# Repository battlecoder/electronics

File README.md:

# electronics
Small Hardware projects that you will most likely find described in my blog: blog.damnsoft.org

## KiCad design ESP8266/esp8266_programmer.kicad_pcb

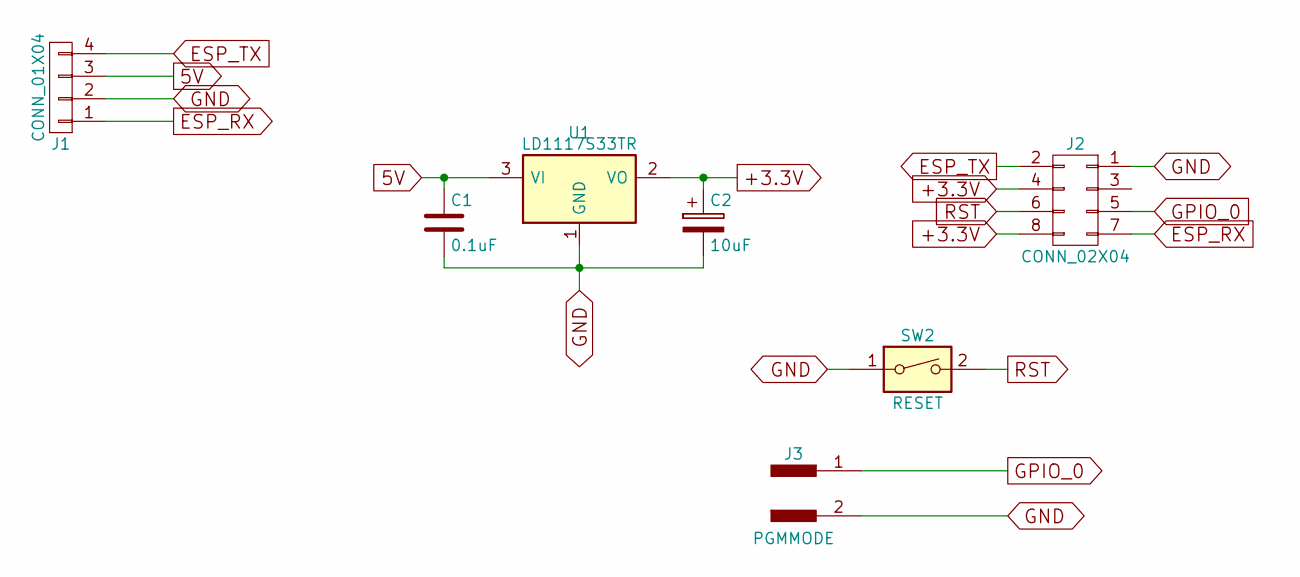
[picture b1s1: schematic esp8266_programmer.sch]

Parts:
C1: 0.1uF; C_Disc_D5.0mm_W2.5mm_P2.50mm
C2: 10uF; CP_Radial_D5.0mm_P2.50mm
J1: CONN_01X04; Pin_Header_Angled_1x04_Pitch2.54mm
J2: CONN_02X04; Socket_Strip_Straight_2x04_Pitch2.54mm
J3: PGMMODE; Pin_Header_Straight_1x02_Pitch2.54mm
SW2: RESET; SW_PUSH_6mm
U1: LD1117S33TR; TO-220-3_Vertical

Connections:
5V: C1.1, J1.3, U1.3 (VI)
+3.3V: C2.1, J2.4, J2.8, U1.2 (VO)
ESP_RX: J1.1, J2.7
ESP_TX: J1.4, J2.2
GND: C1.2, C2.2, J1.2, J2.1, J3.2, SW2.1, U1.1 (GND)
GPIO_0: J2.5, J3.1
RST: J2.6, SW2.2

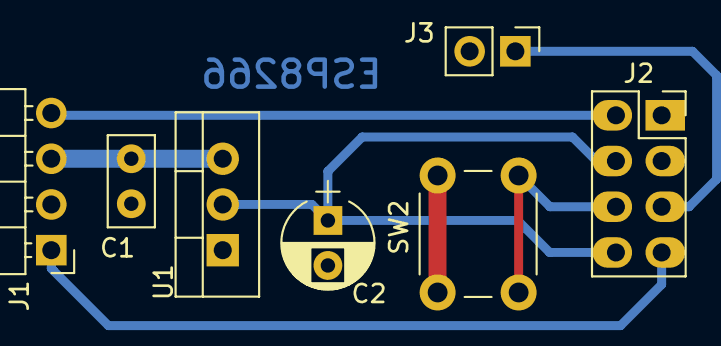
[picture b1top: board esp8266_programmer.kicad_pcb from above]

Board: 2 copper layers, 7 parts (0 on the bottom side), 7 nets.

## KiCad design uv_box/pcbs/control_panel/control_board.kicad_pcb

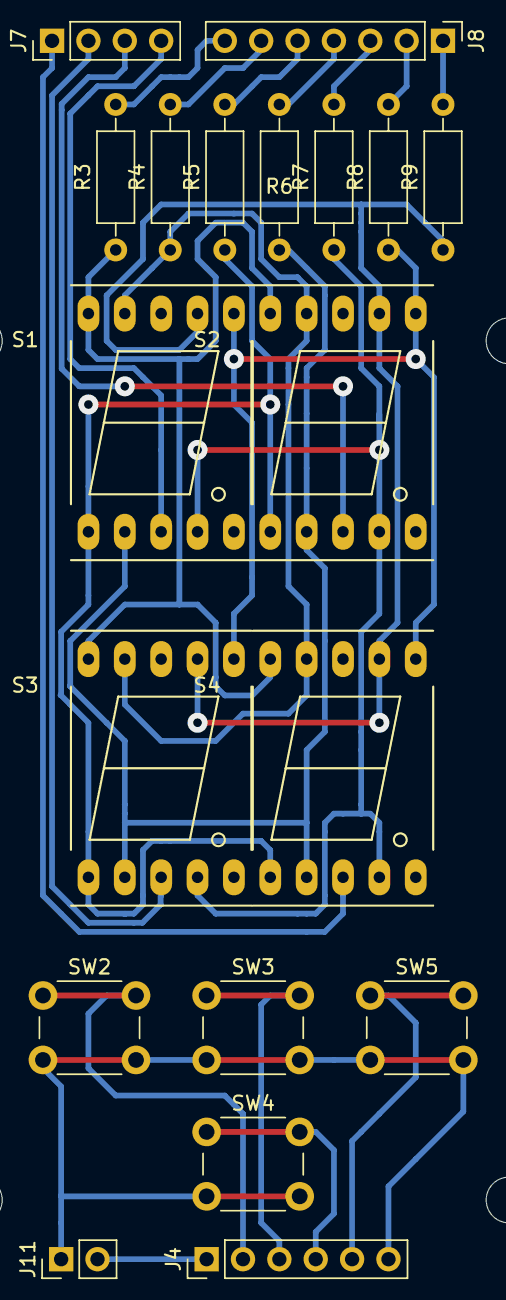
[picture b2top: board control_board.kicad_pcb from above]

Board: 2 copper layers, 19 parts (0 on the bottom side), 24 nets.

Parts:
J4: INPUTS2; Pin_Header_Straight_1x06_Pitch2.54mm
J7: 7SEG_DIGITS2; Pin_Header_Straight_1x04_Pitch2.54mm
J8: 7SEG_SEGMENTS2; Pin_Header_Straight_1x07_Pitch2.54mm
J11: REED; Pin_Header_Straight_1x02_Pitch2.54mm
R3, R4, R5, R6, R7, R8, R9: 100; R_Axial_DIN0207_L6.3mm_D2.5mm_P10.16mm_Horizontal
S1, S2, S3, S4: 7SEGM; 7SegmentLED_LTS6760_LTS6780
SW2, SW3, SW4, SW5: SW_Push; SW_PUSH_6mm

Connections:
DIG1: J7.4, S1.3
DIG2: J7.3, S2.3
DIG3: J7.2, S3.3
DIG4: J7.1, S4.3
unnamed: J4.2, SW2.1
unnamed: J4.3, SW3.1
unnamed: J4.4, SW4.1
unnamed: J4.5, SW5.1
unnamed: J8.1, R9.2
unnamed: J8.2, R8.2
unnamed: J8.3, R7.2
unnamed: J8.4, R6.2
unnamed: J8.5, R5.2
unnamed: J8.6, R4.2
unnamed: J8.7, R3.2
unnamed: J4.6, J11.1, SW2.2, SW3.2, SW4.2, SW5.2
unnamed: J4.1, J11.2
SEG1: R9.1, S1.7, S2.7, S3.7, S4.7
SEG2: R8.1, S1.6, S2.6, S3.6, S4.6
SEG3: R7.1, S1.4, S2.4, S3.4, S4.4
SEG4: R6.1, S1.2, S2.2, S3.2, S4.2
SEG5: R5.1, S1.1, S2.1, S3.1, S4.1
SEG6: R4.1, S1.9, S2.9, S3.9, S4.9
SEG7: R3.1, S1.10, S2.10, S3.10, S4.10

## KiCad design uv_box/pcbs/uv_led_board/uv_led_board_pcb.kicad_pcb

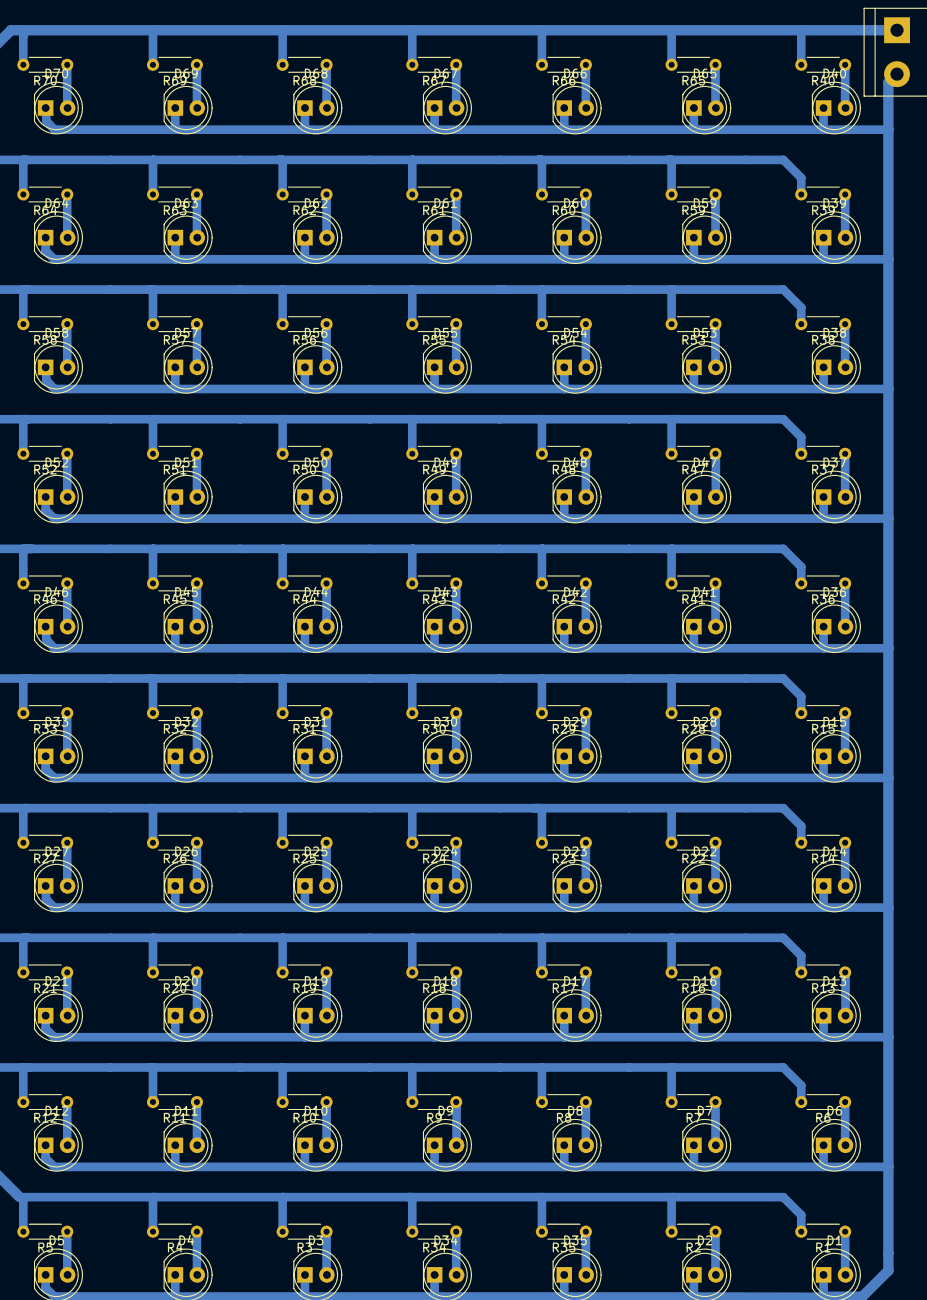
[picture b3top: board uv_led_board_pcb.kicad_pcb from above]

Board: 2 copper layers, 141 parts (0 on the bottom side), 72 nets.

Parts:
D1, D2, D3, D4, D5, D6, D7, D8, D9, D10, D11, D12, D13, D14, D15, D16, D17, D18, D19, D20, D21, D22, D23, D24, D25, D26, D27, D28, D29, D30, D31, D32, D33, D34, D35, D36, D37, D38, D39, D40, D41, D42, D43, D44, D45, D46, D47, D48, D49, D50, D51, D52, D53, D54, D55, D56, D57, D58, D59, D60, D61, D62, D63, D64, D65, D66, D67, D68, D69, D70: LED; LED_D5.0mm
J1: Screw_Terminal_1x02; bornier2
R1, R2, R3, R4, R5, R6, R7, R8, R9, R10, R11, R12, R13, R14, R15, R16, R17, R18, R19, R20, R21, R22, R23, R24, R25, R26, R27, R28, R29, R30, R31, R32, R33, R34, R35, R36, R37, R38, R39, R40, R41, R42, R43, R44, R45, R46, R47, R48, R49, R50, R51, R52, R53, R54, R55, R56, R57, R58, R59, R60, R61, R62, R63, R64, R65, R66, R67, R68, R69, R70: 100; R_Axial_DIN0204_L3.6mm_D1.6mm_P5.08mm_Horizontal

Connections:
+5V: J1.1, R1.2, R2.2, R3.2, R4.2, R5.2, R6.2, R7.2, R8.2, R9.2, R10.2, R11.2, R12.2, R13.2, R14.2, R15.2, R16.2, R17.2, R18.2, R19.2, R20.2, R21.2, R22.2, R23.2, R24.2, R25.2, R26.2, R27.2, R28.2, R29.2, R30.2, R31.2, R32.2, R33.2, R34.2, R35.2, R36.2, R37.2, R38.2, R39.2, R40.2, R41.2, R42.2, R43.2, R44.2, R45.2, R46.2, R47.2, R48.2, R49.2, R50.2, R51.2, R52.2, R53.2, R54.2, R55.2, R56.2, R57.2, R58.2, R59.2, R60.2, R61.2, R62.2, R63.2, R64.2, R65.2, R66.2, R67.2, R68.2, R69.2, R70.2
GND: D1.1, D2.1, D3.1, D4.1, D5.1, D6.1, D7.1, D8.1, D9.1, D10.1, D11.1, D12.1, D13.1, D14.1, D15.1, D16.1, D17.1, D18.1, D19.1, D20.1, D21.1, D22.1, D23.1, D24.1, D25.1, D26.1, D27.1, D28.1, D29.1, D30.1, D31.1, D32.1, D33.1, D34.1, D35.1, D36.1, D37.1, D38.1, D39.1, D40.1, D41.1, D42.1, D43.1, D44.1, D45.1, D46.1, D47.1, D48.1, D49.1, D50.1, D51.1, D52.1, D53.1, D54.1, D55.1, D56.1, D57.1, D58.1, D59.1, D60.1, D61.1, D62.1, D63.1, D64.1, D65.1, D66.1, D67.1, D68.1, D69.1, D70.1, J1.2
unnamed: D1.2, R1.1
unnamed: D2.2, R2.1
unnamed: D3.2, R3.1
unnamed: D4.2, R4.1
unnamed: D5.2, R5.1
unnamed: D6.2, R6.1
unnamed: D7.2, R7.1
unnamed: D8.2, R8.1
unnamed: D9.2, R9.1
unnamed: D10.2, R10.1
unnamed: D11.2, R11.1
unnamed: D12.2, R12.1
unnamed: D13.2, R13.1
unnamed: D14.2, R14.1
unnamed: D15.2, R15.1
unnamed: D16.2, R16.1
unnamed: D17.2, R17.1
unnamed: D18.2, R18.1
unnamed: D19.2, R19.1
unnamed: D20.2, R20.1
unnamed: D21.2, R21.1
unnamed: D22.2, R22.1
unnamed: D23.2, R23.1
unnamed: D24.2, R24.1
unnamed: D25.2, R25.1
unnamed: D26.2, R26.1
unnamed: D27.2, R27.1
unnamed: D28.2, R28.1
unnamed: D29.2, R29.1
unnamed: D30.2, R30.1
unnamed: D31.2, R31.1
unnamed: D32.2, R32.1
unnamed: D33.2, R33.1
unnamed: D34.2, R34.1
unnamed: D35.2, R35.1
unnamed: D36.2, R36.1
unnamed: D37.2, R37.1
unnamed: D38.2, R38.1
unnamed: D39.2, R39.1
unnamed: D40.2, R40.1
unnamed: D41.2, R41.1
unnamed: D42.2, R42.1
unnamed: D43.2, R43.1
unnamed: D44.2, R44.1
unnamed: D45.2, R45.1
unnamed: D46.2, R46.1
unnamed: D47.2, R47.1
unnamed: D48.2, R48.1
unnamed: D49.2, R49.1
unnamed: D50.2, R50.1
unnamed: D51.2, R51.1
unnamed: D52.2, R52.1
unnamed: D53.2, R53.1
unnamed: D54.2, R54.1
unnamed: D55.2, R55.1
unnamed: D56.2, R56.1
unnamed: D57.2, R57.1
unnamed: D58.2, R58.1
unnamed: D59.2, R59.1
unnamed: D60.2, R60.1
unnamed: D61.2, R61.1
unnamed: D62.2, R62.1
unnamed: D63.2, R63.1
unnamed: D64.2, R64.1
unnamed: D65.2, R65.1
unnamed: D66.2, R66.1
unnamed: D67.2, R67.1
unnamed: D68.2, R68.1
unnamed: D69.2, R69.1
unnamed: D70.2, R70.1

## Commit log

2016-06-09 Year is no longer displayed. Date is displayed in a more friendly and descriptive way. The 7SEG char map changed to allow this. Some additional macros were created to help reduce repetition in the co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
2016-06-09 Converted tabs to spaces for consistency across text editors
2016-06-16 Fixed the code that wasn't restoring the write protect flag of the DS1302 after setting time and date, which made the clock vunerable to random halts due to noise, apparently. Also time is queried ev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
2016-07-03 HW revision 1.1. Added a 0.1uF capacitor to improve electric stability and reduce drifting. Also removed version number from the pcb filenames (it's embedded in the schematic and pcb layout now). Fir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
2017-06-25 Hw revision 2.0 (compact board). Firmware updated to reflect that. Several small modifications made for better behavior.
2017-06-27 Added UV Box project
2017-06-27 Added front panel layout (SVG)
2017-06-27 Added overlay SVG file
2017-07-07 Added an alternative full front panel
2018-05-20 Added ESP8266 Programming board
2020-09-14 Improved button handling
    Better / more reliable button detection. Changed mapping of A4 to D0.
